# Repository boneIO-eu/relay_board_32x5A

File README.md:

# Relay Board 32x5A

Documentation you will find here: https://boneio.eu/hardware

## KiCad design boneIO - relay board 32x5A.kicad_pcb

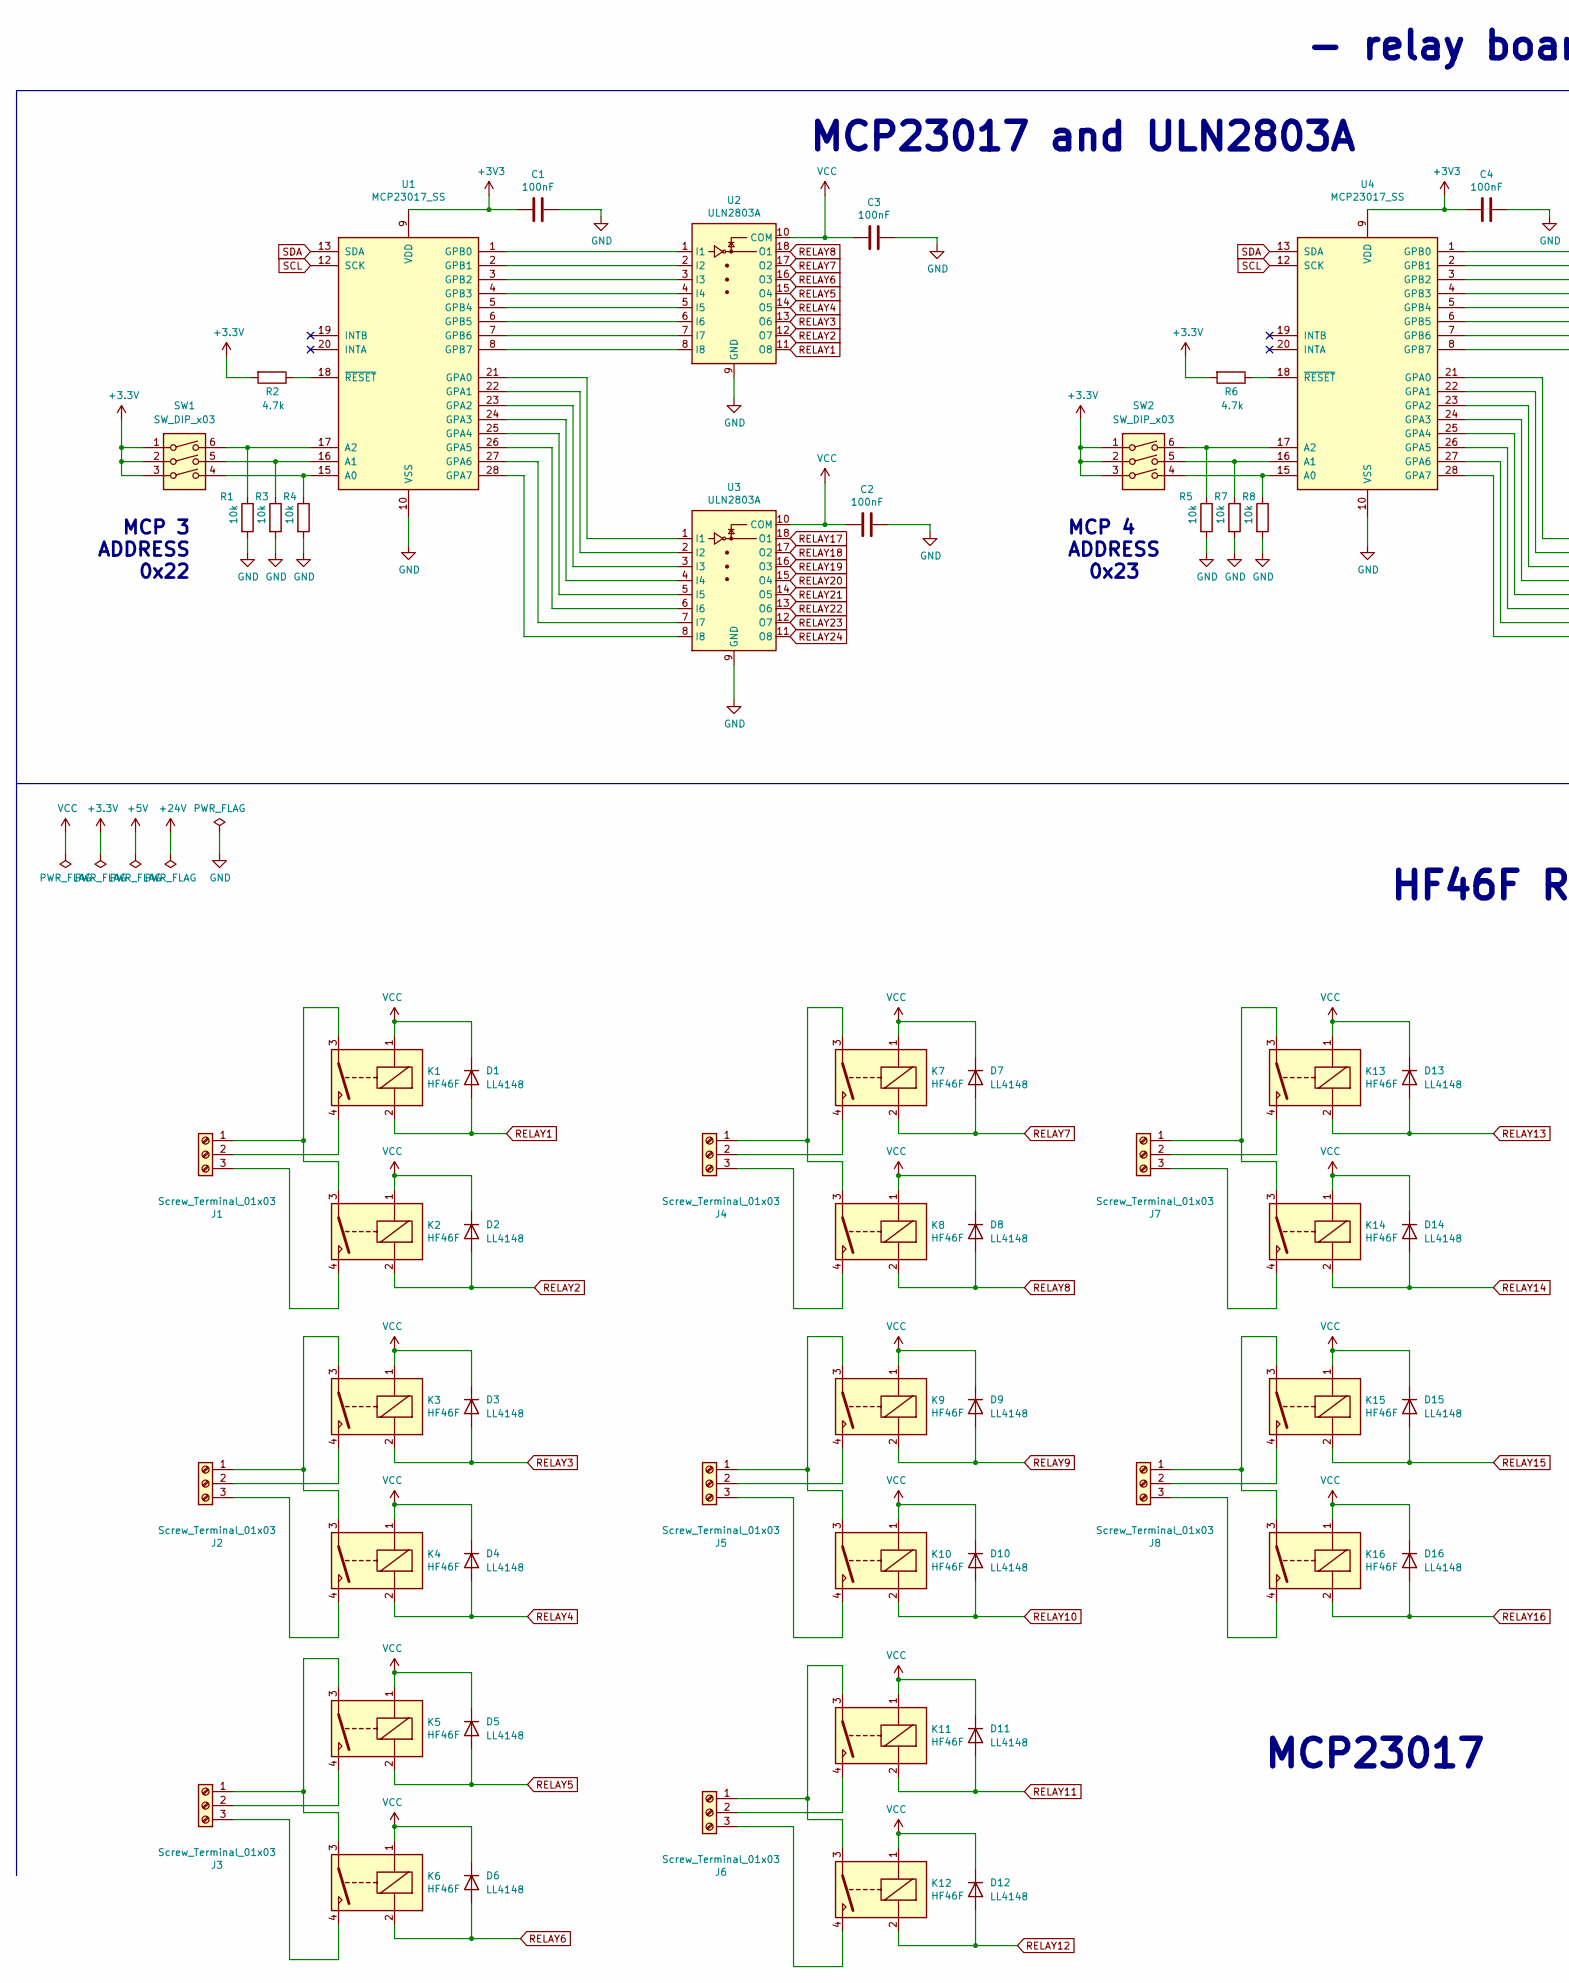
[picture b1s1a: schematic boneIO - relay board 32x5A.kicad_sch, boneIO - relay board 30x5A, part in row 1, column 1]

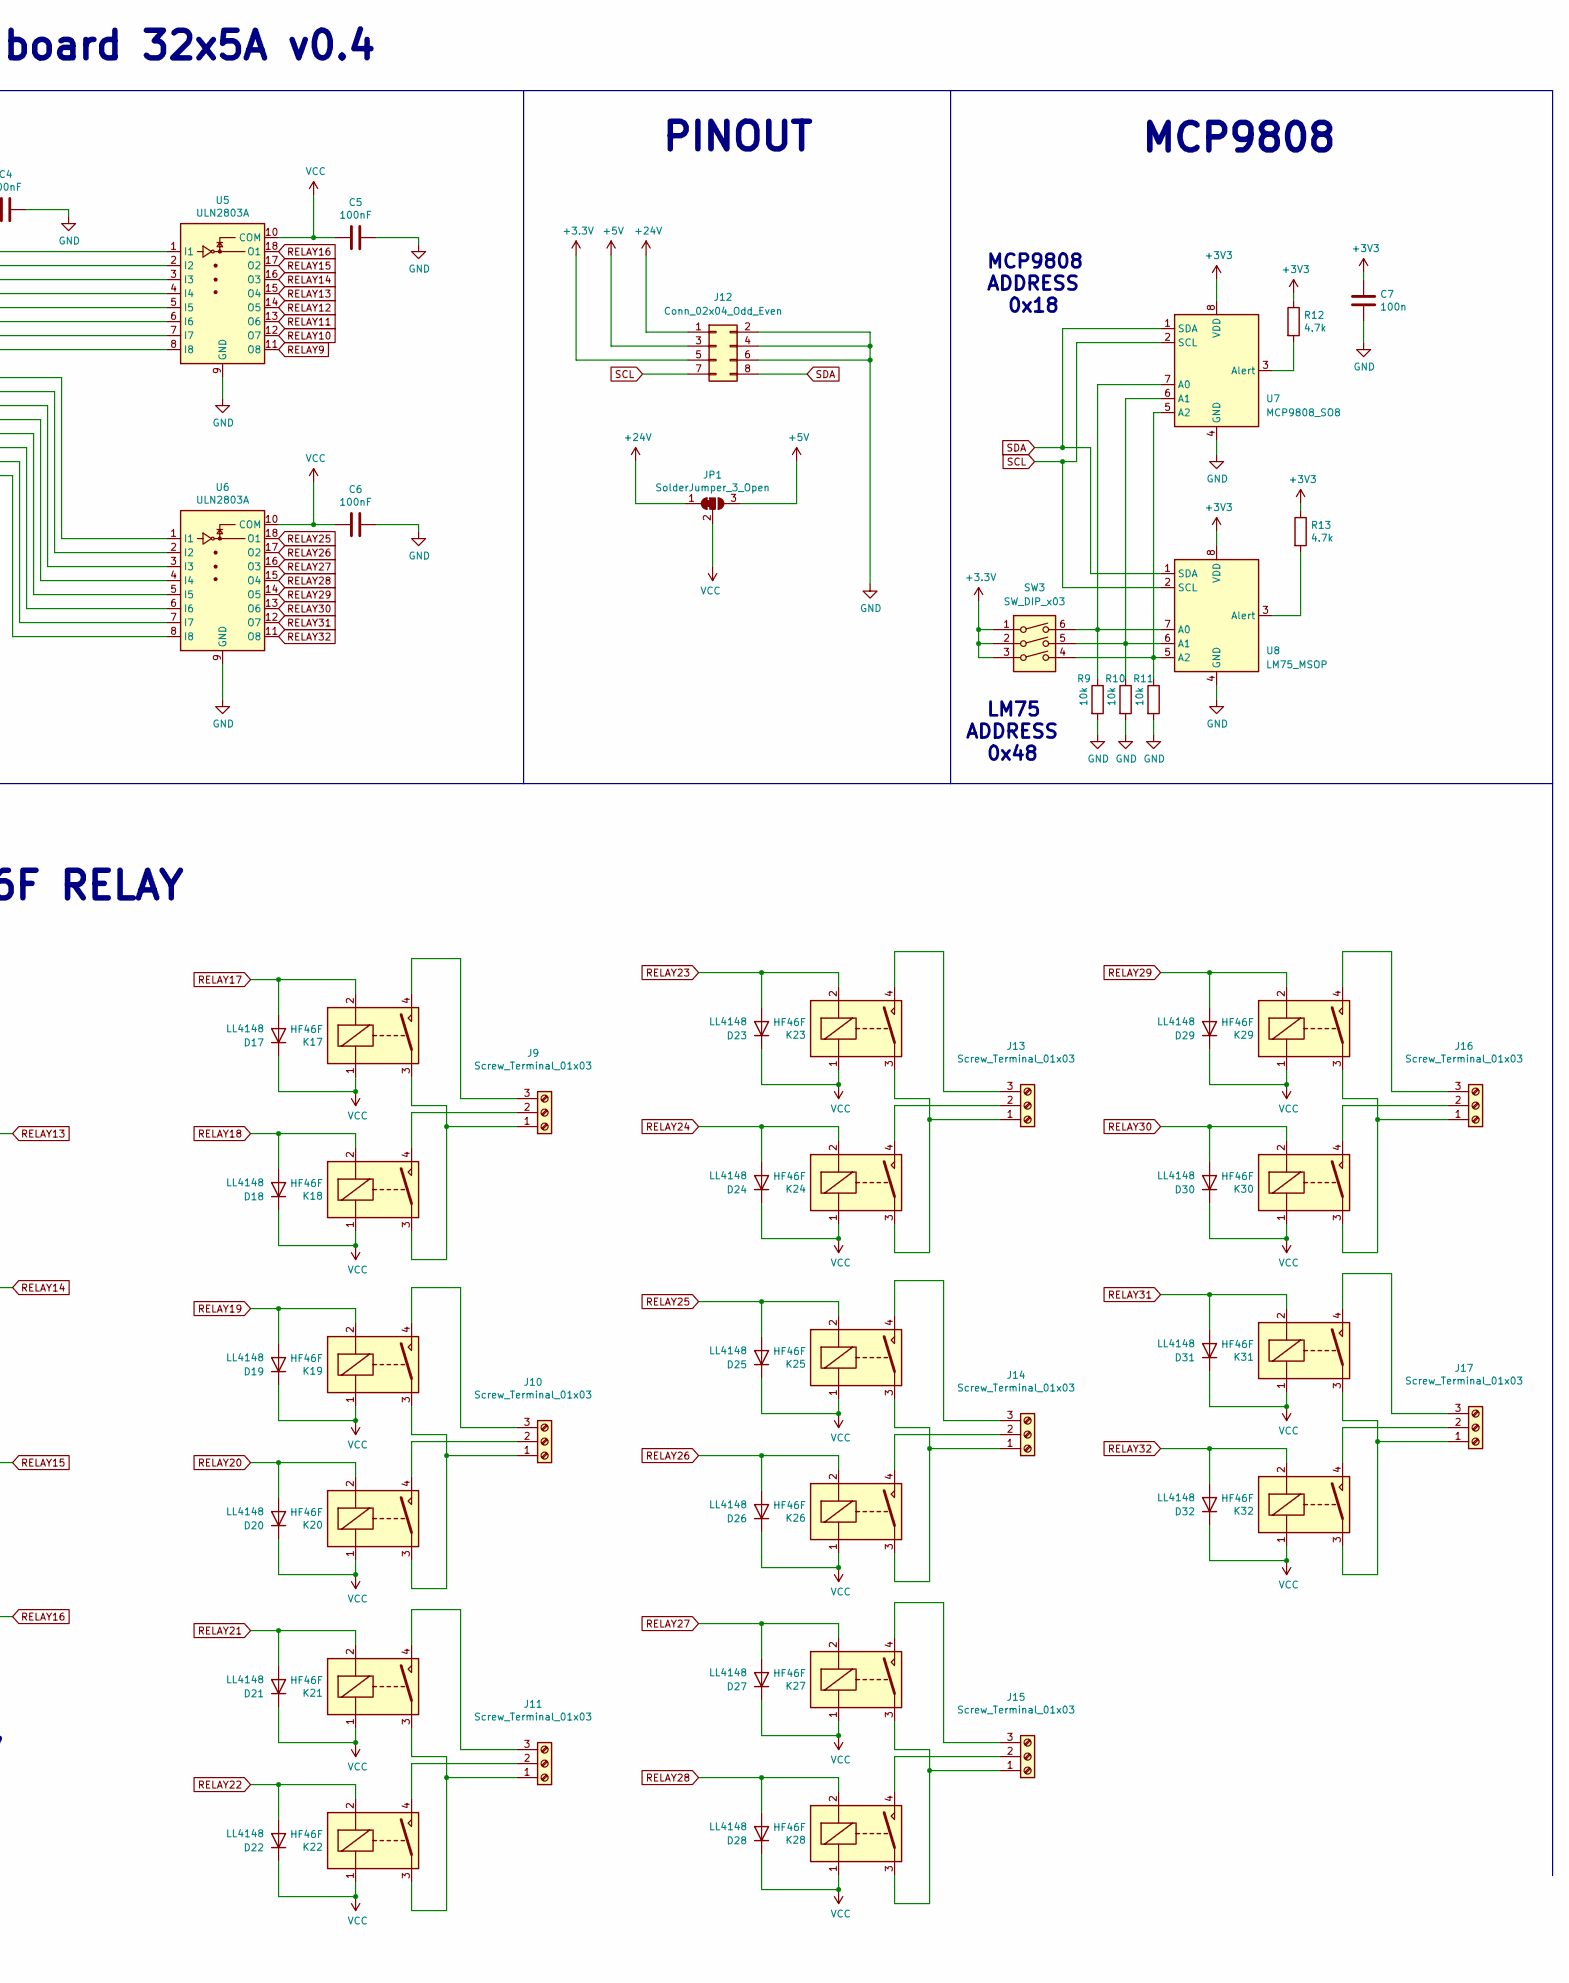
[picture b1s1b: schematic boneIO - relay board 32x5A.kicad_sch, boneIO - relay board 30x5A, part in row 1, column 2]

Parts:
C1, C2, C3, C4, C5, C6: 100nF; C_0603_1608Metric
C7: 100n; C_0603_1608Metric
D1, D2, D3, D4, D5, D6, D7, D8, D9, D10, D11, D12, D13, D14, D15, D16, D17, D18, D19, D20, D21, D22, D23, D24, D25, D26, D27, D28, D29, D30, D31, D32: LL4148; D_MiniMELF
J1, J2, J3, J4, J5, J6, J7, J8, J9, J10, J11, J13, J14, J15, J16, J17: Screw_Terminal_01x03; PhoenixContact_GMSTBA_2,5_3-G_1x03_P7.50mm_Horizontal
J12: Conn_02x04_Odd_Even; PinHeader_2x04_P2.54mm_Vertical
JP1: SolderJumper_3_Open; SolderJumper-3_P1.3mm_Bridged12_RoundedPad1.0x1.5mm
K1, K2, K3, K4, K5, K6, K7, K8, K9, K10, K11, K12, K13, K14, K15, K16, K17, K18, K19, K20, K21, K22, K23, K24, K25, K26, K27, K28, K29, K30, K31, K32: HF46F
R1, R3, R4, R5, R7, R8, R9, R10, R11: 10k; R_0603_1608Metric
R2, R6, R12, R13: 4.7k; R_0603_1608Metric
SW1, SW2, SW3: SW_DIP_x03; SW_DIP_SPSTx03_Slide_Omron_A6S-310x_W8.9mm_P2.54mm
U1, U4: MCP23017_SS; SSOP-28_5.3x10.2mm_P0.65mm
U2, U3, U5, U6: ULN2803A; SOIC-18W_7.5x11.6mm_P1.27mm
U7: MCP9808_SO8; SO-8_3.9x4.9mm_P1.27mm
U8: LM75_MSOP; MSOP-8_3x3mm_P0.65mm

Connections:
+5V: J12.3, JP1.3 (B)
+24V: J12.1, JP1.1 (A)
GND: C1.1, C2.1, C3.1, C4.1, C5.1, C6.1, C7.2, J12.2, J12.4, J12.6, R1.2, R3.2, R4.2, R5.2, R7.2, R8.2, R9.2, R10.2, R11.2, U1.10 (VSS), U2.9 (GND), U3.9 (GND), U4.10 (VSS), U5.9 (GND), U6.9 (GND), U7.4 (GND), U8.4 (GND)
unnamed: J1.1, K1.3, K2.3
unnamed: J1.2, K1.4
unnamed: J1.3, K2.4
unnamed: J2.1, K3.3, K4.3
unnamed: J2.2, K3.4
unnamed: J2.3, K4.4
unnamed: J3.1, K5.3, K6.3
unnamed: J3.2, K5.4
unnamed: J3.3, K6.4
unnamed: J4.1, K7.3, K8.3
unnamed: J4.2, K7.4
unnamed: J4.3, K8.4
unnamed: J5.1, K9.3, K10.3
unnamed: J5.2, K9.4
unnamed: J5.3, K10.4
unnamed: J6.1, K11.3, K12.3
unnamed: J6.2, K11.4
unnamed: J6.3, K12.4
unnamed: J7.1, K13.3, K14.3
unnamed: J7.2, K13.4
unnamed: J7.3, K14.4
unnamed: J8.1, K15.3, K16.3
unnamed: J8.2, K15.4
unnamed: J8.3, K16.4
unnamed: J9.1, K17.3, K18.3
unnamed: J9.2, K18.4
unnamed: J9.3, K17.4
unnamed: J10.1, K19.3, K20.3
unnamed: J10.2, K20.4
unnamed: J10.3, K19.4
unnamed: J11.1, K21.3, K22.3
unnamed: J11.2, K22.4
unnamed: J11.3, K21.4
unnamed: J13.1, K23.3, K24.3
unnamed: J13.2, K24.4
unnamed: J13.3, K23.4
unnamed: J14.1, K25.3, K26.3
unnamed: J14.2, K26.4
unnamed: J14.3, K25.4
unnamed: J15.1, K27.3, K28.3
unnamed: J15.2, K28.4
unnamed: J15.3, K27.4
unnamed: J16.1, K29.3, K30.3
unnamed: J16.2, K30.4
unnamed: J16.3, K29.4
unnamed: J17.1, K31.3, K32.3
unnamed: J17.2, K32.4
unnamed: J17.3, K31.4
unnamed: R1.1, SW1.6, U1.17 (A2)
unnamed: R2.1, U1.18 (~RESET)
unnamed: R3.1, SW1.5, U1.16 (A1)
unnamed: R4.1, SW1.4, U1.15 (A0)
unnamed: R5.1, SW2.6, U4.17 (A2)
unnamed: R6.1, U4.18 (~RESET)
unnamed: R7.1, SW2.5, U4.16 (A1)
unnamed: R8.1, SW2.4, U4.15 (A0)
unnamed: R9.1, SW3.6, U7.7 (A0), U8.7 (A0)
unnamed: R10.1, SW3.5, U7.6 (A1), U8.6 (A1)
unnamed: R11.1, SW3.4, U7.5 (A2), U8.5 (A2)
unnamed: R12.2, U7.3 (Alert)
unnamed: R13.2, U8.3 (Alert)
unnamed: U1.1 (GPB0), U2.1 (I1)
unnamed: U1.2 (GPB1), U2.2 (I2)
unnamed: U1.3 (GPB2), U2.3 (I3)
unnamed: U1.4 (GPB3), U2.4 (I4)
unnamed: U1.5 (GPB4), U2.5 (I5)
unnamed: U1.6 (GPB5), U2.6 (I6)
unnamed: U1.7 (GPB6), U2.7 (I7)
unnamed: U1.8 (GPB7), U2.8 (I8)
unnamed: U1.21 (GPA0), U3.1 (I1)
unnamed: U1.22 (GPA1), U3.2 (I2)
unnamed: U1.23 (GPA2), U3.3 (I3)
unnamed: U1.24 (GPA3), U3.4 (I4)
unnamed: U1.25 (GPA4), U3.5 (I5)
unnamed: U1.26 (GPA5), U3.6 (I6)
unnamed: U1.27 (GPA6), U3.7 (I7)
unnamed: U1.28 (GPA7), U3.8 (I8)
unnamed: U4.1 (GPB0), U5.1 (I1)
unnamed: U4.2 (GPB1), U5.2 (I2)
unnamed: U4.3 (GPB2), U5.3 (I3)
unnamed: U4.4 (GPB3), U5.4 (I4)
unnamed: U4.5 (GPB4), U5.5 (I5)
unnamed: U4.6 (GPB5), U5.6 (I6)
unnamed: U4.7 (GPB6), U5.7 (I7)
unnamed: U4.8 (GPB7), U5.8 (I8)
unnamed: U4.21 (GPA0), U6.1 (I1)
unnamed: U4.22 (GPA1), U6.2 (I2)
unnamed: U4.23 (GPA2), U6.3 (I3)
unnamed: U4.24 (GPA3), U6.4 (I4)
unnamed: U4.25 (GPA4), U6.5 (I5)
unnamed: U4.26 (GPA5), U6.6 (I6)
unnamed: U4.27 (GPA6), U6.7 (I7)
unnamed: U4.28 (GPA7), U6.8 (I8)
RELAY1: D1.2 (A), K1.2, U2.11 (O8)
RELAY2: D2.2 (A), K2.2, U2.12 (O7)
RELAY3: D3.2 (A), K3.2, U2.13 (O6)
RELAY4: D4.2 (A), K4.2, U2.14 (O5)
RELAY5: D5.2 (A), K5.2, U2.15 (O4)
RELAY6: D6.2 (A), K6.2, U2.16 (O3)
RELAY7: D7.2 (A), K7.2, U2.17 (O2)
RELAY8: D8.2 (A), K8.2, U2.18 (O1)
RELAY9: D9.2 (A), K9.2, U5.11 (O8)
RELAY10: D10.2 (A), K10.2, U5.12 (O7)
RELAY11: D11.2 (A), K11.2, U5.13 (O6)
RELAY12: D12.2 (A), K12.2, U5.14 (O5)
RELAY13: D13.2 (A), K13.2, U5.15 (O4)
RELAY14: D14.2 (A), K14.2, U5.16 (O3)
RELAY15: D15.2 (A), K15.2, U5.17 (O2)
RELAY16: D16.2 (A), K16.2, U5.18 (O1)
RELAY17: D17.2 (A), K17.2, U3.18 (O1)
RELAY18: D18.2 (A), K18.2, U3.17 (O2)
RELAY19: D19.2 (A), K19.2, U3.16 (O3)
RELAY20: D20.2 (A), K20.2, U3.15 (O4)
RELAY21: D21.2 (A), K21.2, U3.14 (O5)
RELAY22: D22.2 (A), K22.2, U3.13 (O6)
RELAY23: D23.2 (A), K23.2, U3.12 (O7)
RELAY24: D24.2 (A), K24.2, U3.11 (O8)
RELAY25: D25.2 (A), K25.2, U6.18 (O1)
RELAY26: D26.2 (A), K26.2, U6.17 (O2)
RELAY27: D27.2 (A), K27.2, U6.16 (O3)
RELAY28: D28.2 (A), K28.2, U6.15 (O4)
RELAY29: D29.2 (A), K29.2, U6.14 (O5)
RELAY30: D30.2 (A), K30.2, U6.13 (O6)
RELAY31: D31.2 (A), K31.2, U6.12 (O7)
RELAY32: D32.2 (A), K32.2, U6.11 (O8)
SCL: J12.7, U1.12 (SCK), U4.12 (SCK), U7.2 (SCL), U8.2 (SCL)
SDA: J12.8, U1.13 (SDA), U4.13 (SDA), U7.1 (SDA), U8.1 (SDA)
VCC: C2.2, C3.2, C5.2, C6.2, D1.1 (K), D2.1 (K), D3.1 (K), D4.1 (K), D5.1 (K), D6.1 (K), D7.1 (K), D8.1 (K), D9.1 (K), D10.1 (K), D11.1 (K), D12.1 (K), D13.1 (K), D14.1 (K), D15.1 (K), D16.1 (K), D17.1 (K), D18.1 (K), D19.1 (K), D20.1 (K), D21.1 (K), D22.1 (K), D23.1 (K), D24.1 (K), D25.1 (K), D26.1 (K), D27.1 (K), D28.1 (K), D29.1 (K), D30.1 (K), D31.1 (K), D32.1 (K), JP1.2 (C), K1.1, K2.1, K3.1, K4.1, K5.1, K6.1, K7.1, K8.1, K9.1, K10.1, K11.1, K12.1, K13.1, K14.1, K15.1, K16.1, K17.1, K18.1, K19.1, K20.1, K21.1, K22.1, K23.1, K24.1, K25.1, K26.1, K27.1, K28.1, K29.1, K30.1, K31.1, K32.1, U2.10 (COM), U3.10 (COM), U5.10 (COM), U6.10 (COM)

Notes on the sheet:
PINOUT
MCP23017 and ULN2803A
MCP 3 ADDRESS 0x22
LM75 ADDRESS 0x48
MCP23017
MCP 4 ADDRESS 0x23
HF46F RELAY
MCP9808
- relay board 32x5A v0.4
MCP9808 ADDRESS 0x18

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
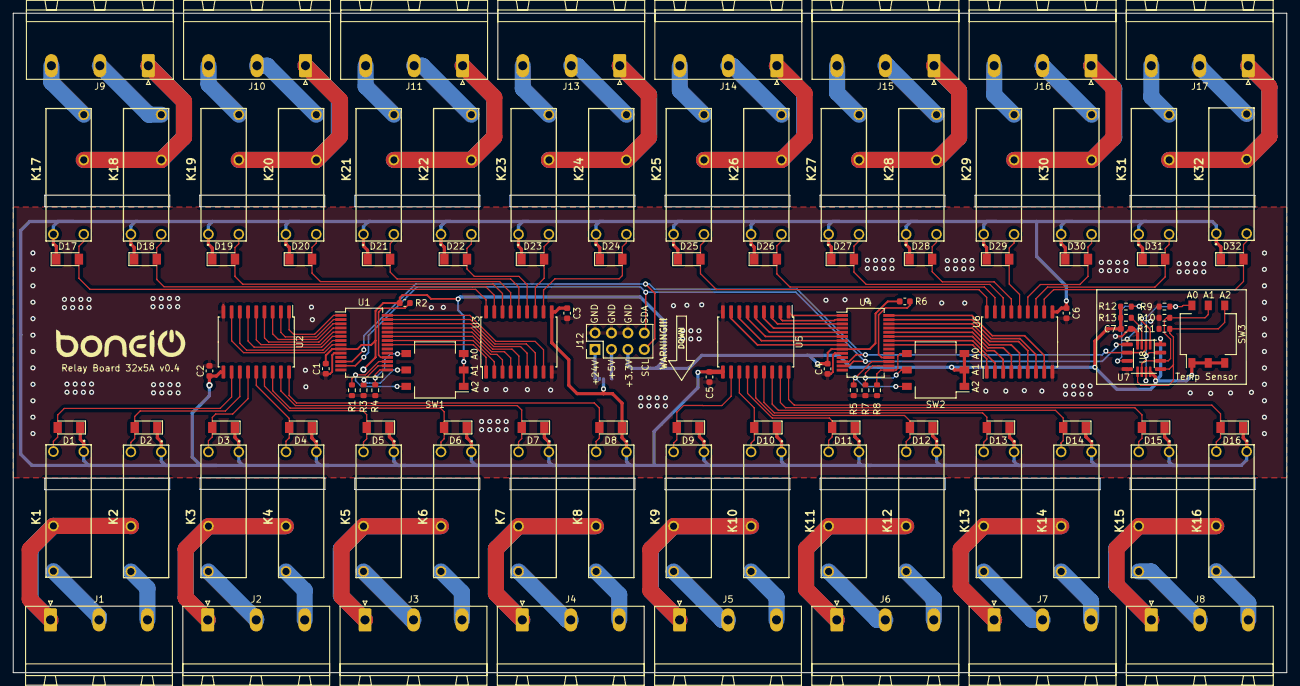
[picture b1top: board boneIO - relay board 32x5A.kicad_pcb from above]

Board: 2 copper layers, 197.0 x 102.0 mm, 113 parts (1 on the bottom side), 132 nets.

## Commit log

2021-11-05 Renamed files to 32x5A
2021-11-10 relay 32x5 directory cleanup
    added shared library with footprints
2021-11-10 merge
2021-11-10 Changed board labels
2021-11-19 correcting the scheme
2021-12-04 32x5 v0.3
2022-01-17 Directory cleanup
2022-01-17 Create LICENSE
2022-01-28 Added photo of the board
2022-05-16 Added top render
2022-05-16 Changed photo
2022-05-17 relay_board_32x5A_v0.4
    v0.4
2022-05-17 Repo cleanup for release v0.4
